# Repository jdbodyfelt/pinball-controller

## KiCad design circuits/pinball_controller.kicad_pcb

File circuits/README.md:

# Pinball Apron Console - for Virtual Pinball Wizards

## System Outline

The console controller is comprised of a number of systems, similar to `/lib` coding structures. 
Here, we focus on the circuitry associated with the device. 

### The Button Array

Let's start with your standard pinball controls. I've extended flipper/magna to a four-button offset stack. 
That should address several user configurations! This yields 8 "side action" buttons. In addition to this, 
there are three front panel buttons - a left "start game" and "next ball", and a right "launch".

All buttons have LED illumination - which discussed in next section. This just covers the 

### LED Array Drivers 

* Side Button Array 
* Front Button Array
* Exterior Strips

### The Sensors Array

* Accelerometer - Virtual Tilt Plumb
* Time-of-Flight - Virtual Spring Ball Plunger

### The Power Array 

I'm using an upcycled Sony VGP-AC19V31 power adapter from an old laptop. It's 19.5V @ 4.7A (90W), delivered
via     barrel positive tip. I create two isolated power lines: 

* +12V High Amperage - for solenoids, motors, vibrators, shockers, & other haptics. May drive exterior LEDs. 
* +5V Mid-to-High Amperage - for many MCU units (like TLC5947). Also powers most of the button 5V LED arrays. 
* +3.3V Lo Amperage - Logic voltage, strip off w/ LDO!

<Discuss Circuit Here>

###

###

###

###

###

###

###

## Power

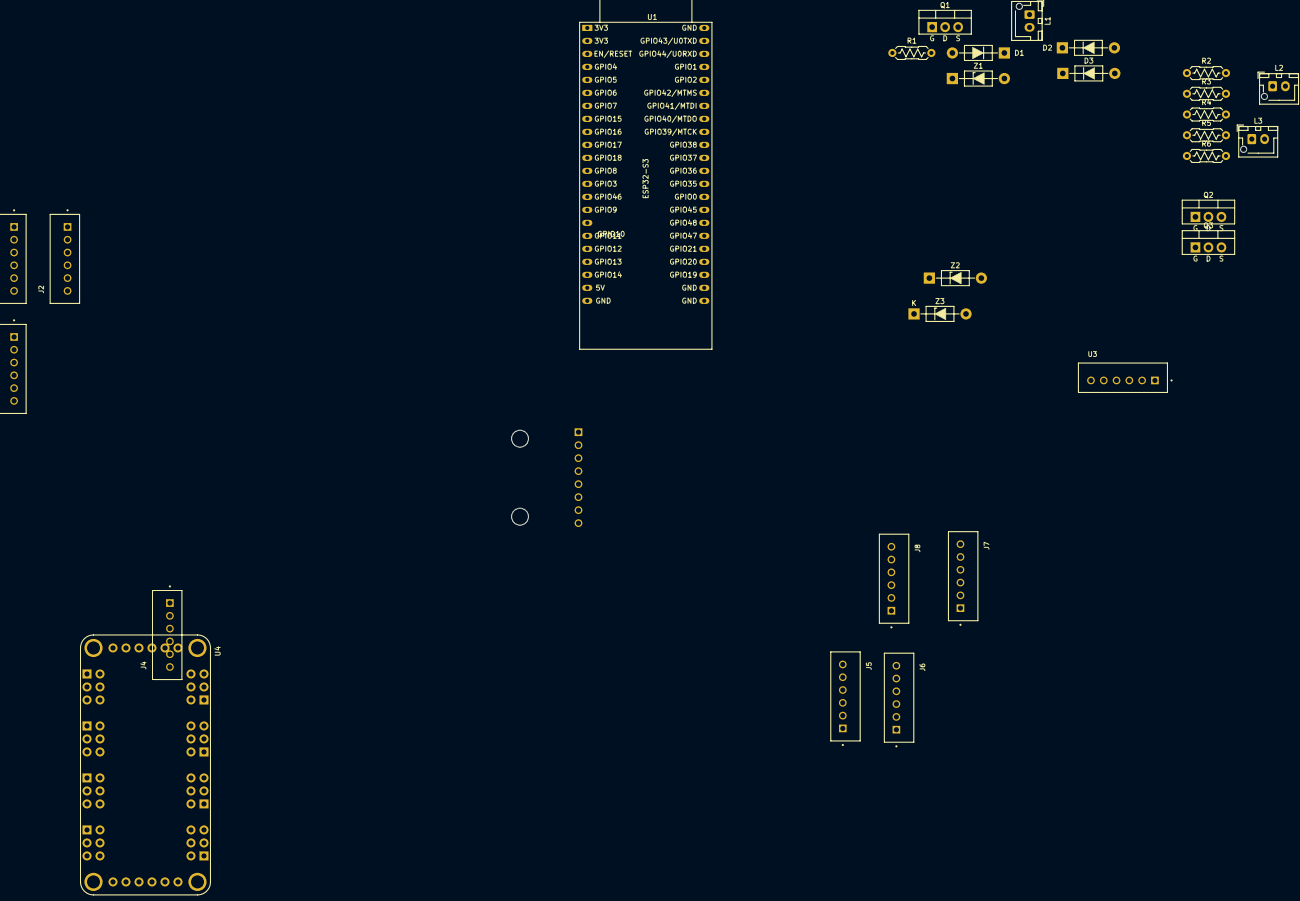
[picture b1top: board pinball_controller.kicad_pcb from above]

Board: 2 copper layers, 30 parts (1 on the bottom side), 52 nets, no tracks yet.

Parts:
D1, D2, D3: UF4007; D_DO-41_SOD81_P10.16mm_Horizontal
J1: Left Upper Flipper; B6B-XH-A
J2: Left Upper Magna; B6B-XH-A
J3: Left Lower Flipper; B6B-XH-A
J4: Left Lower Magna; B6B-XH-A
J5: Right Upper Flipper; B6B-XH-A
J6: Right Upper Magna; B6B-XH-A
J7: Right Lower Flipper; B6B-XH-A
J8: Right Lower Magna; B6B-XH-A
L1, L2, L3: JF0530B; JST_XH_B2B-XH-AM_1x02_P2.50mm_Vertical
Q1, Q2, Q3: IRFZ44N; TO-220-3_Vertical_GDS
R1, R3, R5: 100; R_Axial_DIN0207_L6.3mm_D2.5mm_P7.62mm_Horizontal
R2, R4, R6: 10K; R_Axial_DIN0207_L6.3mm_D2.5mm_P7.62mm_Horizontal
U1: ESP32-S3; ESP32-S3-DevKitC
U2: SEN-09836; SEN-09836 (ADXL345 Dev Board)
U3: VL8160X; B6B-XH-A
U4: TLC5947; ADA1914-TLC5947
Z1, Z2, Z3: 1N4744A; D_DO-41_SOD81_P10.16mm_Horizontal_Zener

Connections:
+3V3: U1.1 (3V3), U1.2 (3V3), U2.2 (VCC), U2.3 (CS), U3.1 (VIN), U3.6 (SHUT)
+5V: U1.21 (5V), U4.JP1_6 (V+), U4.JP2_1 (24V_1), U4.JP2_3 (24V_1), U4.JP2_5 (24V_1), U4.JP3_1 (24V_1), U4.JP3_3 (24V_1), U4.JP3_5 (24V_1), U4.JP4_1 (24V_1), U4.JP4_3 (24V_1), U4.JP4_5 (24V_1), U4.JP5_1 (24V_2), U4.JP5_3 (24V_2), U4.JP5_5 (24V_2), U4.JP6_1 (24V_2), U4.JP6_3 (24V_2), U4.JP6_5 (24V_2), U4.JP7_1 (24V_2), U4.JP7_3 (24V_2), U4.JP7_5 (24V_3), U4.JP8_1 (24V_3), U4.JP8_3 (24V_3), U4.JP8_5 (24V_3), U4.JP9_1 (24V_3), U4.JP9_3 (24V_3), U4.JP9_5 (24V_3), U4.JP10_6 (V+)
+12V: D1.1 (K), D2.1 (K), D3.1 (K), L1.2, L2.2, L3.2
/LED Bank/CLK: U1.38 (GPIO41/MTDI), U4.JP1_3 (CLK), U4.JP10_3 (CLK)
/LED Bank/DIN: U1.39 (GPIO42/MTMS), U4.JP1_4 (DIN)
/LED Bank/LAT: U1.36 (GPIO39/MTCK), U4.JP1_1 (LAT), U4.JP10_1 (LAT)
/LED Bank/SW_LLF: J3.4, U1.9 (GPIO16/ADC2_CH5/32K_N)
/LED Bank/SW_LLM: J4.4, U1.8 (GPIO15/ADC2_CH4/32K_P)
/LED Bank/SW_LUF: J1.4, U1.11 (GPIO18/ADC2_CH7)
/LED Bank/SW_LUM: J2.4, U1.10 (GPIO17/ADC2_CH6)
/LED Bank/SW_RLF: J7.4, U1.18 (GPIO12/ADC2_CH1)
/LED Bank/SW_RLM: J8.4, U1.17 (GPIO11/ADC2_CH0)
/LED Bank/SW_RUF: J5.4, U1.20 (GPIO14/ADC2_CH3)
/LED Bank/SW_RUM: J6.4, U1.19 (GPIO13/ADC2_CH2)
/LED Bank/~OE: U1.37 (GPIO40/MTDO), U4.JP1_2 (~OE), U4.JP10_2 (~OE)
/Thumper Array/COIL_CENTER: R5.1, U1.40 (GPIO2/ADC1_CH1)
/Thumper Array/COIL_LEFT: R1.1, U1.41 (GPIO1/ADC1_CH0)
/Thumper Array/COIL_RIGHT: R3.1, U1.13 (GPIO3/ADC1_CH2)
GND: J1.1, J1.5, J2.1, J2.5, J3.1, J3.5, J4.1, J4.5, J5.1, J5.5, J6.1, J6.5, J7.1, J7.5, J8.1, J8.5, U1.22 (GND), U1.23 (GND), U1.24 (GND), U1.44 (GND), U2.1 (GND), U2.6 (SDO), U3.2 (GND), U4.JP1_5 (GND), U4.JP10_5 (GND)
GNDPWR: Q1.3 (S), Q2.3 (S), Q3.3 (S), R2.2, R4.2, R6.2, Z1.2 (A), Z2.2 (A), Z3.2 (A)
unnamed: D1.2 (A), L1.1, Q1.2 (D)
unnamed: D2.2 (A), L2.1, Q2.2 (D)
unnamed: D3.2 (A), L3.1, Q3.2 (D)
unnamed: Q1.1 (G), R1.2, R2.1, Z1.1 (K)
unnamed: Q2.1 (G), R3.2, R4.1, Z2.1 (K)
unnamed: Q3.1 (G), R5.2, R6.1, Z3.1 (K)
unnamed: J1.6, U4.JP2_2 (OUT0)
unnamed: J1.3, U4.JP2_4 (OUT1)
unnamed: J1.2, U4.JP2_6 (OUT2)
unnamed: J2.6, U4.JP3_2 (OUT3)
unnamed: J2.3, U4.JP3_4 (OUT4)
unnamed: J2.2, U4.JP3_6 (OUT5)
unnamed: J3.6, U4.JP4_2 (OUT6)
unnamed: J3.3, U4.JP4_4 (OUT7)
unnamed: J3.2, U4.JP4_6 (OUT8)
unnamed: J4.6, U4.JP5_2 (OUT9)
unnamed: J4.3, U4.JP5_4 (OUT10)
unnamed: J4.2, U4.JP5_6 (OUT11)
unnamed: J5.6, U4.JP6_2 (OUT12)
unnamed: J5.3, U4.JP6_4 (OUT13)
unnamed: J5.2, U4.JP6_6 (OUT14)
unnamed: J6.6, U4.JP7_2 (OUT15)
unnamed: J6.3, U4.JP7_4 (OUT16)
unnamed: J6.2, U4.JP7_6 (OUT17)
unnamed: J7.6, U4.JP8_2 (OUT18)
unnamed: J7.3, U4.JP8_4 (OUT19)
unnamed: J7.2, U4.JP8_6 (OUT20)
unnamed: J8.6, U4.JP9_2 (OUT21)
unnamed: J8.3, U4.JP9_4 (OUT22)
unnamed: J8.2, U4.JP9_6 (OUT23)
SCL: U1.15 (GPIO9/ADC1_CH8), U2.8 (SCL), U3.4 (SCL)
SDA: U1.12 (GPIO8/ADC1_CH7), U2.7 (SDA), U3.3 (SDA)

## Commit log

2025-10-25 TiltSensor build completed!
2025-10-25 Checked changing freqs
2025-10-25 Updated to do
2025-10-26 Play with Formatting - Introduced Vector class
2025-10-27 Playing with HID
2025-10-28 Started refactor with GOOD libraries
2025-10-29 Working - comms to PC next
2025-10-29 Added Butterworth filtering
2025-10-30 Sweet! Full pitch & roll calculated. Need to run a normalizer though.
2025-10-30 Gamepad start
2025-10-31 Work on cleanup
2025-11-03 Major refactors, reduce to Adafruit lib
2025-11-03 Looking at filters
2025-11-04 Joystick is implemented
2025-11-04 Looks good; may need dead zone on Joystick
2025-11-05 ArcadeButton & RangeLaser built; Proper ArcadeButton pinout image
2025-11-05 Updated box design notes
2025-11-05 Added notes
2025-11-07 Added first Haptic
2025-11-10 KiCad Updates
